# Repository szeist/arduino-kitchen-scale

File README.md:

# Arduino Kitchen Scale with binary display

## Parts

1. 1x HX711 Load cell amplifier
3. 1x Straight bar load cell (2kg)
4. 1x Charlieplexed led array with 12 leds *(See schematics)*

## Requirements

1. [HX711_ADC](https://github.com/olkal/HX711_ADC) library
2. [CHPLX12](https://github.com/szeist/CHPLX12) library

## Calibrate

### 1. Upload calibration firmware

Define CALIBRATE_MODE in `firmware.ino`, complile and upload the firmware.

### 2. Put a known weightd item to the scale and use the serial interface for calibration

Connect to the serial port and use the following keys to adjust the measured weight:

| Key | Calibration Value |
| --- | ----------------- |
| `h` | +1                |
| `H` | +10               |
| `l` | -1                |
| `L` | -10               |
| `t` | Tare              |

### 3. Update the calibration factor

Update the `DEFAULT_CAL_FACTOR` in the `firmware.ino` with the new CalFactor value.

## Display

### Generate gerber files for production

1. Plot the PCB
    - Layers:
        - F.Cu
        - B.Cu
        - B.SilkS
        - F.SilkS
        - B.Mask
        - F.Mask
        - Edge.Cuts
    - Options:
        - [X] Use Protel filename extensions
        - [ ] Include extended attributes
        - [ ] Subtract soldermask from silkscreen

2. Generate drill file with the following options:
    - **Millimeters** as drill units
    - **Supress leading** zeros as zeros format
    - **PostScript** as drill map format

3. Rename all files with the `schematics/scripts/rename_gerber_files.sh` script

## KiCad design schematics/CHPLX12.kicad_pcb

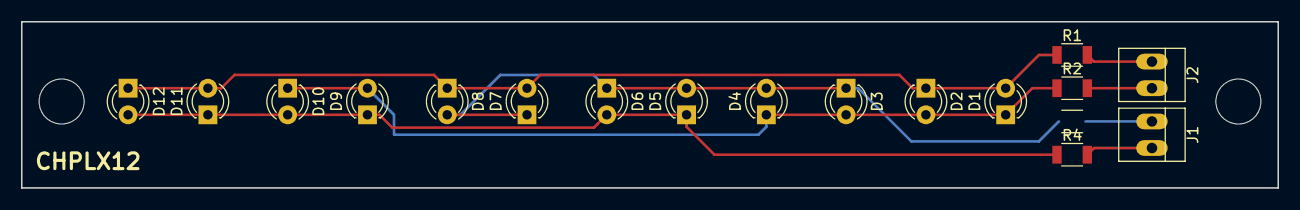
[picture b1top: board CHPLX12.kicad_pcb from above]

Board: 2 copper layers, 120.0 x 15.9 mm, 18 parts (0 on the bottom side), 8 nets.

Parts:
D1, D2, D3, D4, D5, D6, D7, D8, D9, D10, D11, D12: LED; LED_D3.0mm
J1, J2: PINHEAD1-2
R1, R2, R3, R4: 220; R_1206

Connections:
unnamed: D1.1, D2.2, D3.2, D4.1, D9.2, D10.1, R2.1
unnamed: D1.2, D2.1, D7.2, D8.1, D11.2, D12.1, R1.1
unnamed: D3.1, D4.2, D5.2, D6.1, D7.1, D8.2, R3.1
unnamed: D5.1, D6.2, D9.1, D10.2, D11.1, D12.2, R4.1
PIN1: J2.1, R1.2
PIN2: J2.2, R2.2
PIN3: J1.1, R3.2
PIN4: J1.2, R4.2

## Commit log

2018-06-07 Add firmware
2018-06-22 add display schematics
2018-06-22 extrace display driver
2018-06-22 cleanup
2019-02-02 add display pcb design with gerber files
2019-02-02 fix readme
2019-02-02 remove unnecessary wire from pcb
2019-02-02 ad bak from readme
